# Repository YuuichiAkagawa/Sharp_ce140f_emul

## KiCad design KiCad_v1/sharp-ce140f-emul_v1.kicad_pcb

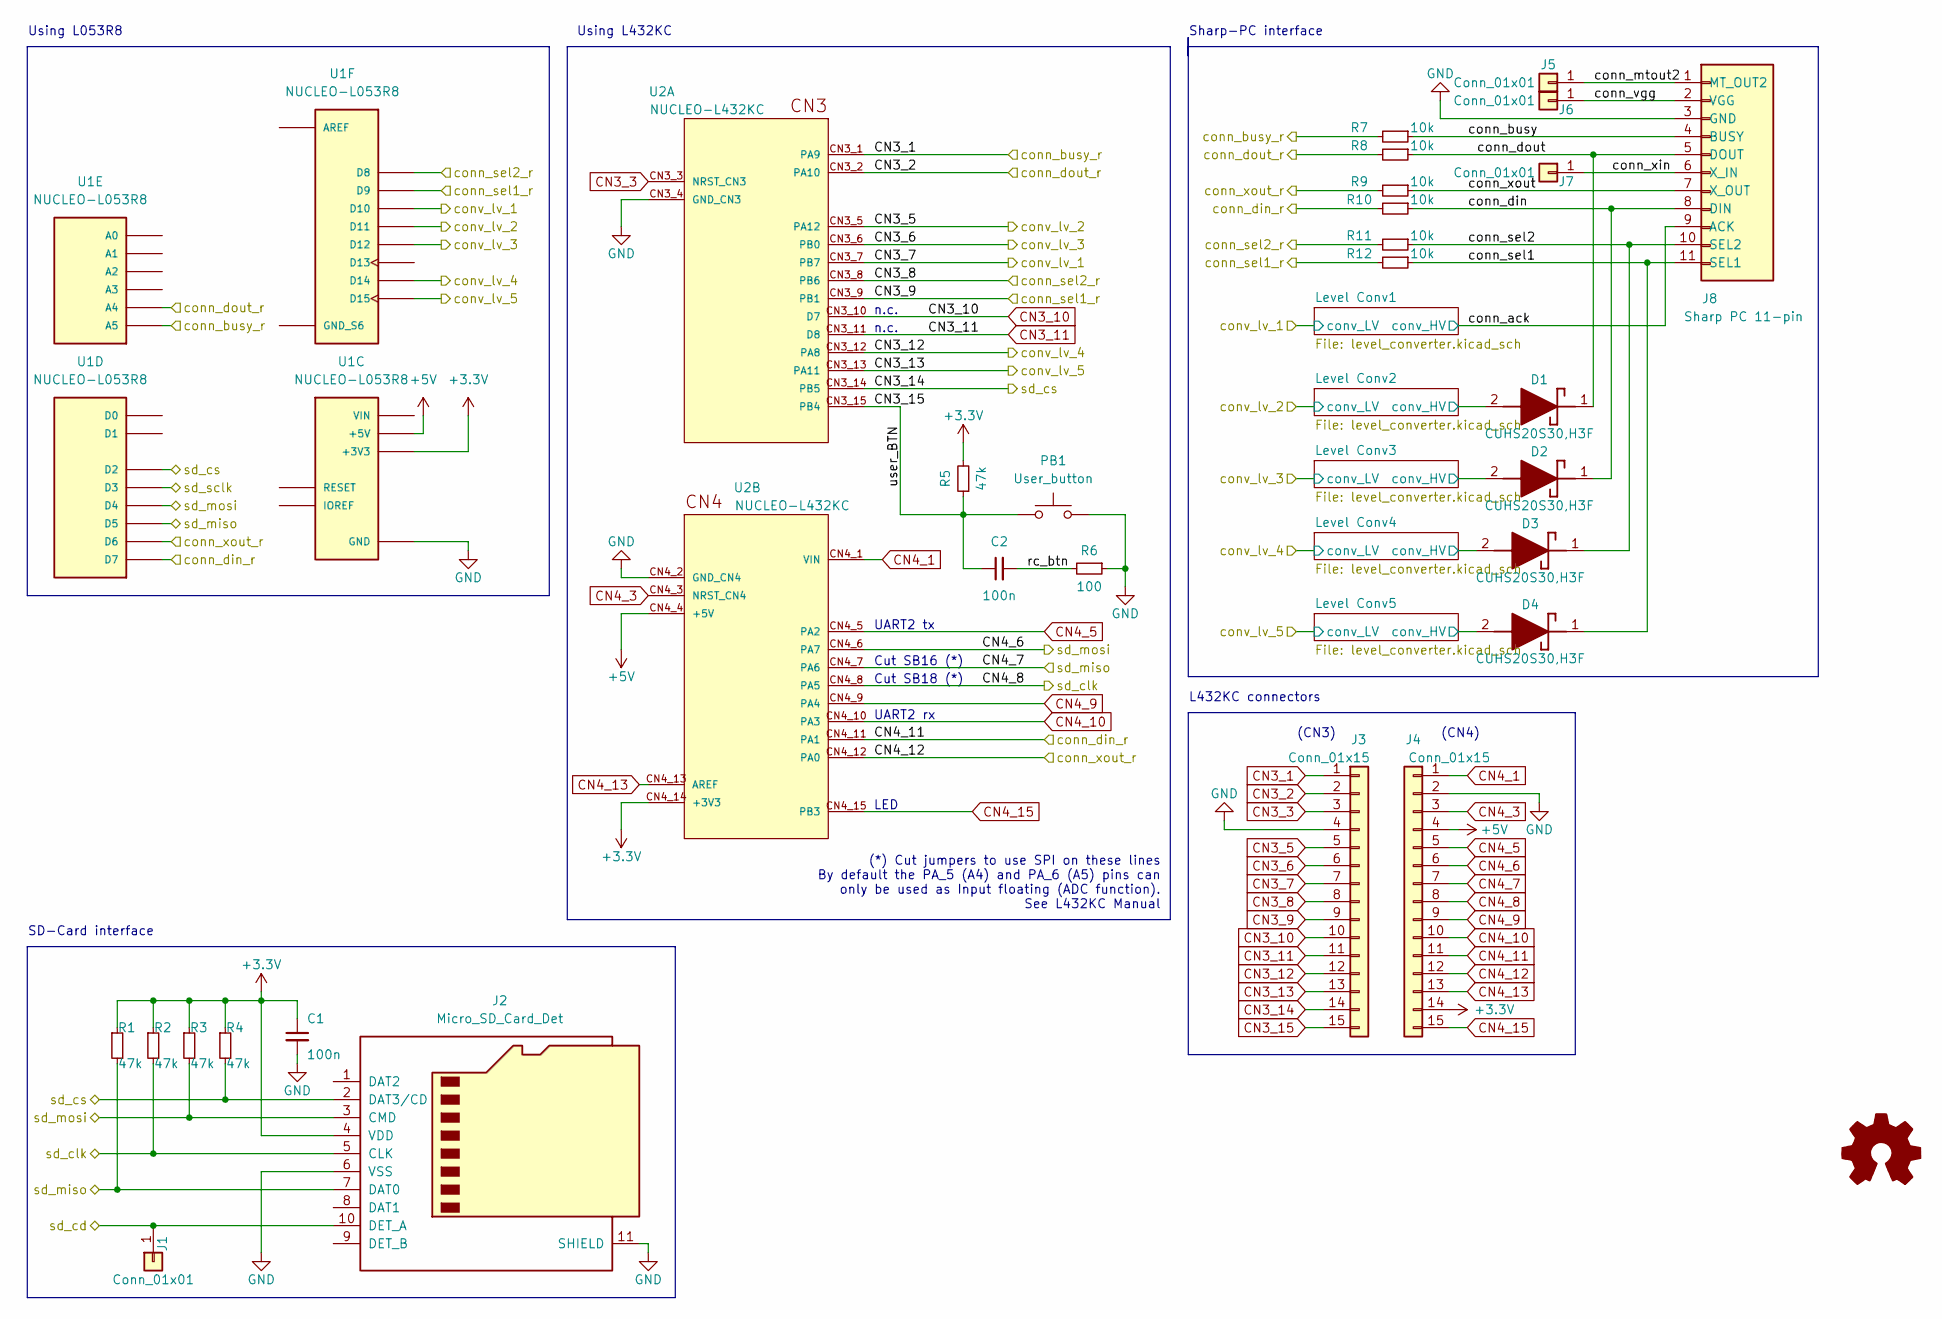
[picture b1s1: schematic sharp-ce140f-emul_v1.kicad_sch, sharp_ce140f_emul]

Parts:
C1, C2: 100n; C_0603_1608Metric_Pad1.08x0.95mm_HandSolder
D1, D2, D3, D4: CUHS20S30,H3F; CUHS20S40H3F; Manufacturer_Part_Number CUHS20S30,H3F; Mouser Part Number 757-CUHS20S30H3F
J1, J5, J6, J7: Conn_01x01; Pin_D0.7mm_L6.5mm_W1.8mm_FlatFork
J2: Micro_SD_Card_Det; microSD_HC_Molex_104031-0811
J3, J4: Conn_01x15; PinHeader_1x15_P2.54mm_Vertical
J8: Sharp PC 11-pin; PinHeader_1x11_P2.54mm_Horizontal
PB1: User_button; SW_Push_1P1T_NO_6x6mm_H9.5mm
R1, R2, R3, R4, R5: 47k; R_0603_1608Metric_Pad0.98x0.95mm_HandSolder
R6: 100; R_0603_1608Metric_Pad0.98x0.95mm_HandSolder
R7, R8, R9, R10, R11, R12: 10k; R_0603_1608Metric_Pad0.98x0.95mm_HandSolder
U1: NUCLEO-L053R8; ST_NUCLEO-F401RE; PARTREV 13
U2: NUCLEO-L432KC; MODULE_NUCLEO-L432KC; PARTREV N/A

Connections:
+3V3: C1.1, J2.4 (VDD), J4.14, R1.1, R2.1, R3.1, R4.1, R5.2, U1.CN6_4 (+3V3), U2.CN4_14 (+3V3)
+5V: J4.4, U1.CN6_5 (+5V), U2.CN4_4 (+5V); also elsewhere on the board
/Level Conv2/conv_HV: D1.2 (A); also elsewhere on the board
/Level Conv3/conv_HV: D2.2 (A); also elsewhere on the board
/Level Conv4/conv_HV: D3.2 (A); also elsewhere on the board
/Level Conv5/conv_HV: D4.2 (A); also elsewhere on the board
/conn_ack: J8.9 (ACK); also elsewhere on the board
/conn_busy: J8.4 (BUSY), R7.1
/conn_din: D2.1 (K), J8.8 (DIN), R10.1
/conn_dout: D1.1 (K), J8.5 (DOUT), R8.1
/conn_mtout2: J5.1, J8.1 (MT_OUT2)
/conn_sel1: D4.1 (K), J8.11 (SEL1), R12.1
/conn_sel2: D3.1 (K), J8.10 (SEL2), R11.1
/conn_vgg: J6.1, J8.2 (VGG)
/conn_xin: J7.1, J8.6 (X_IN)
/conn_xout: J8.7 (X_OUT), R9.1
/rc_btn: C2.2, R6.2
/sd_cd: J1.1, J2.10 (DET_A)
CN3_1: J3.1, R7.2, U1.CN8_6 (A5), U2.CN3_1 (PA9)
CN3_2: J3.2, R8.2, U1.CN8_5 (A4), U2.CN3_2 (PA10)
CN3_3: J3.3, U2.CN3_3 (NRST_CN3)
CN3_5: J3.5, U1.CN5_4 (D11), U2.CN3_5 (PA12); also elsewhere on the board
CN3_6: J3.6, U1.CN5_5 (D12), U2.CN3_6 (PB0); also elsewhere on the board
CN3_7: J3.7, U1.CN5_3 (D10), U2.CN3_7 (PB7); also elsewhere on the board
CN3_8: J3.8, R11.2, U1.CN5_1 (D8), U2.CN3_8 (PB6)
CN3_9: J3.9, R12.2, U1.CN5_2 (D9), U2.CN3_9 (PB1)
CN3_10: J3.10, U2.CN3_10 (D7)
CN3_11: J3.11, U2.CN3_11 (D8)
CN3_12: J3.12, U1.CN5_9 (D14), U2.CN3_12 (PA8); also elsewhere on the board
CN3_13: J3.13, U1.CN5_10 (D15), U2.CN3_13 (PA11); also elsewhere on the board
CN3_14: J2.2 (DAT3/CD), J3.14, R4.2, U1.CN9_3 (D2), U2.CN3_14 (PB5)
CN3_15: C2.1, J3.15, PB1.1, R5.1, U2.CN3_15 (PB4)
CN4_1: J4.1, U2.CN4_1 (VIN)
CN4_3: J4.3, U2.CN4_3 (NRST_CN4)
CN4_5: J4.5, U2.CN4_5 (PA2)
CN4_6: J2.3 (CMD), J4.6, R3.2, U1.CN9_5 (D4), U2.CN4_6 (PA7)
CN4_7: J2.7 (DAT0), J4.7, R1.2, U1.CN9_6 (D5), U2.CN4_7 (PA6)
CN4_8: J2.5 (CLK), J4.8, R2.2, U2.CN4_8 (PA5)
CN4_9: J4.9, U2.CN4_9 (PA4)
CN4_10: J4.10, U2.CN4_10 (PA3)
CN4_11: J4.11, R10.2, U1.CN9_8 (D7), U2.CN4_11 (PA1)
CN4_12: J4.12, R9.2, U1.CN9_7 (D6), U2.CN4_12 (PA0)
CN4_13: J4.13, U2.CN4_13 (AREF)
CN4_15: J4.15, U2.CN4_15 (PB3)
GND: C1.2, J2.6 (VSS), J2.11 (SHIELD), J3.4, J4.2, J8.3 (GND), PB1.2, R6.1, U1.CN6_6 (GND), U1.CN6_7 (GND), U2.CN3_4 (GND_CN3), U2.CN4_2 (GND_CN4); also elsewhere on the board

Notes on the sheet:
L432KC connectors
UART2 rx
n.c.
Sharp-PC interface
Using L053R8
Cut SB16 (*)
(CN4)
Using L432KC
LED
(CN3)
UART2 tx
(*) Cut jumpers to use SPI on these lines By default the PA_5 (A4) and PA_6 (A5) pins can only be used as Input floating (ADC function). See L432KC Manual
SD-Card interface
Cut SB18 (*)

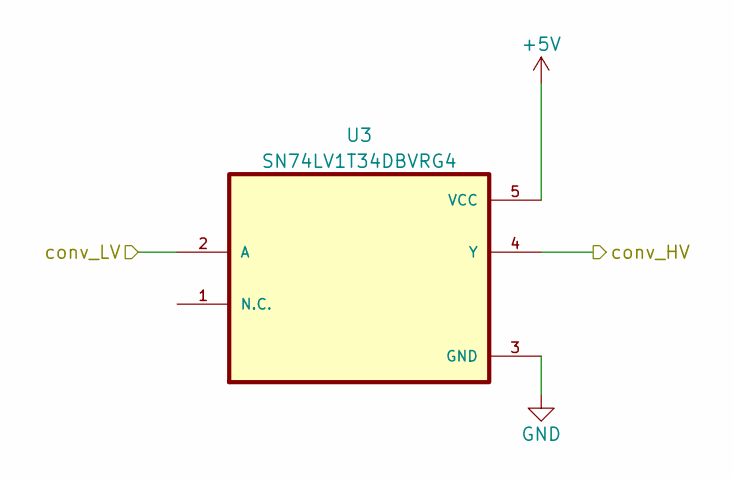
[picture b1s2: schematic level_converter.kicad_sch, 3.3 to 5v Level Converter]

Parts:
U3: SN74LV1T34DBVRG4; SOT95P280X145-5N

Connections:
+5V: U3.5 (VCC); also elsewhere on the board
/conn_ack: U3.4 (Y); also elsewhere on the board
CN3_7: U3.2 (A); also elsewhere on the board
GND: U3.3 (GND); also elsewhere on the board

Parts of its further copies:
U4, U5, U6, U7: SN74LV1T34DBVRG4; SOT95P280X145-5N

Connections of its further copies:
+5V: U4.5 (VCC), U5.5 (VCC), U6.5 (VCC), U7.5 (VCC); also elsewhere on the board
/Level Conv2/conv_HV: U4.4 (Y); also elsewhere on the board
/Level Conv3/conv_HV: U5.4 (Y); also elsewhere on the board
/Level Conv4/conv_HV: U6.4 (Y); also elsewhere on the board
/Level Conv5/conv_HV: U7.4 (Y); also elsewhere on the board
CN3_5: U4.2 (A); also elsewhere on the board
CN3_6: U5.2 (A); also elsewhere on the board
CN3_12: U6.2 (A); also elsewhere on the board
CN3_13: U7.2 (A); also elsewhere on the board
GND: U4.3 (GND), U5.3 (GND), U6.3 (GND), U7.3 (GND); also elsewhere on the board

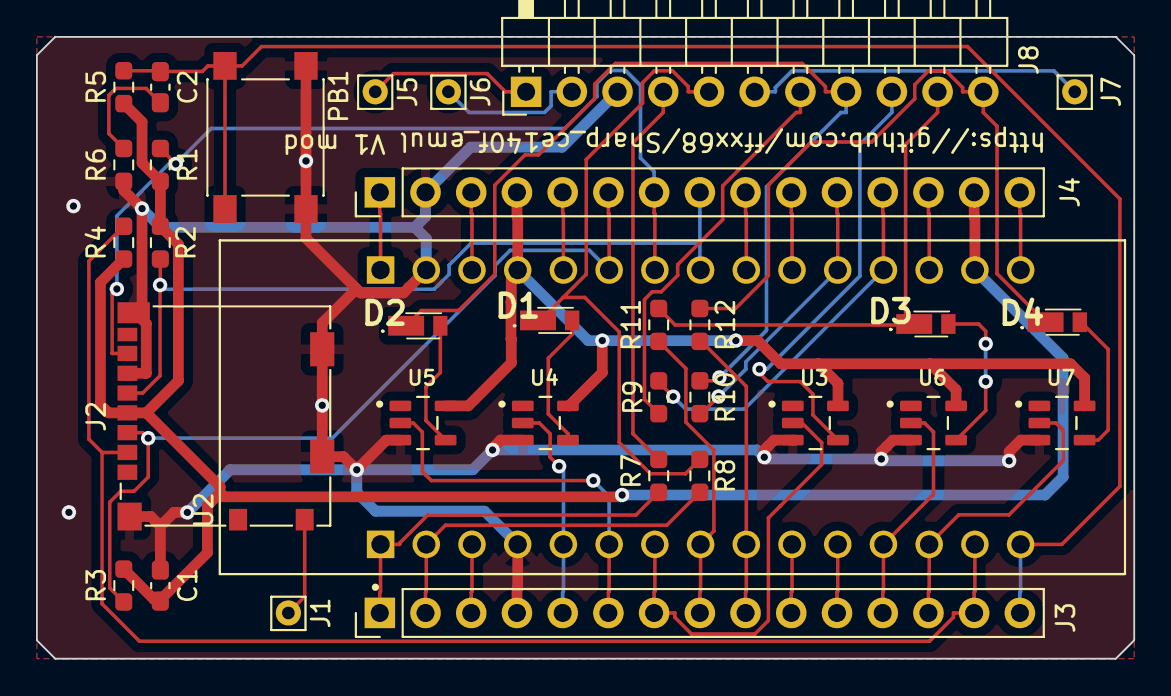
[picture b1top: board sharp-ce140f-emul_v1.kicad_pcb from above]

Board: 2 copper layers, 61.0 x 34.5 mm, 33 parts (0 on the bottom side), 45 nets.

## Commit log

2023-06-18 Level converter changed to 74LV1T34
